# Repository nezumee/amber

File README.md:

# Amber
Personalized split keyboard based on [Zebra](https://github.com/nezumee/zebra) experimentation.

# Bill of material

* PCB x2, switch plate PCB x2, bottom plate PCB x2 (see [gerber](gerber), all PCBs are reversible)
* ProMicro or equivalent x2 (if using something other than ProMicro, check if it will fit in the PCB cutout!)
* Peel-A-Way sockets x48 pins (https://keeb.io/products/peel-a-way-sockets-for-pro-micros)
* Mid-mount TRRS jack x2 (https://www.digikey.com/en/products/detail/cui-devices/SJ-43504-SMT-TR/2625173 or PJ342C in https://www.aliexpress.com/item/1005001299482943.html)
* Tactile switch x2 (https://www.digikey.com/en/products/detail/panasonic-electronic-components/EVQ-P7C01P/4429458)
* RGB LED x2 (https://www.digikey.com/en/products/detail/inolux/HV-5RGB60/7604616 or compatible)
* 1k Ohm resistor in 1206 size x2 (or other value, depending on how bright you want the indicator LED to be)
* EC11 rotary encoders x0-2
* N4148 x32 in DO-35 (through hole) or SOD123 (surface mount) form factor
* KailH sockets x32-34 (you need less than 34 if using encoders)
* Cherry MX compatible switches x32-34
* Keycaps
* TRRS cable

# Making a PCB sandwich keyboard starting with an ergogen definition
This design was created with help of the https://github.com/mrzealot/ergogen tool that makes it easier to generate keyboard plates and PCBs.

Rough steps used:
1. Generate PCB and outlines using ergogen: [ergogen.yaml](ergogen.yaml)
2. Create a Kicad schematic with switches and diodes, matching the ids created by ergogen, make a PCB based on that
3. Overwrite the Kicad PCB with the one coming from ergogen
4. Update PCB from schematic, preserving references but updating the nets and footprints as needed
5. Import the edges layer from ergogen outline, keep default position so outline matches the switch positions
6. Continue designing the PCB in Kicad as normal

# Fitting the ProMicro between the switch plate and PCB
Many keyboards using ProMicro (like Corne) either have the ProMicro exposed, or use a small plate to cover it separately from the switch plate. While the tech prototype look of showing the MCU is nice, sometimes you want something cleaner looking, and also less prone to gathering visible dust. With this in mind, I decided to make the front plate that serves both as a plate for the switches and also covers all the components on the PCB. This led to a few challenges:

1. Fit the ProMicro and its socket (yes, I didn't want to solder it to the PCB directly) between the PCB and the front plate. This required a surprising amount of effort:
  * Use the thinnest sockets I could find - Peel-a-way sockets (https://keeb.io/products/peel-a-way-sockets-for-pro-micros). They seem to be difficult to source, luckily I got some beforehand. Note that these sockets require bigger holes than you would normally have. My first iteration of the PCB had too narrow holes so they could not fit. 1.1mm in the second version is enough:

  * Mount ProMicro upside down
  * Make a cutout in the PCB to fit the components on ProMicro
 
  * The cutout and the fact that ProMicro is stuck between switches and the end of the board made routing quite difficult. Leaving a bridge between the left and right pin columns helped, but common ways of making reversible PCBs couldn't work. There is no space for dual ProMicro footprint, and I cannot reverse the ProMicro either since it becomes too tall to fit. I didn't want to mount it below the PCB either since there's even less space there.
  * To make the PCB reversible, I ended up using different pinouts for the left and right halves. For example, the index finger column (CI) is connected to B2 on the left side, but is mirrored to B4 on the right. This solved most of the pins at the cost of complicating firmware. A few that could not be reassigned, like VCC. For those, I added jumpers that are cut and soldered depending on which side is being built. For left side, you connect J1-J3 and cut J4-J6 (default). For the right side, you do the opposite.
 
2. Fit a TRRS jack between the plates. The jack commonly used is even thicker than ProMicro with a socket. Luckily, it turned out there are special mid-mount jacks that mount into a cutout in the PCB: CUI Devices SJ-4350 series available on DigiKey, or PJ342C available on AliExpress (I got both; despite the differences in diagrams on seller sites, the ones I got look identical).

3. Fit a reset button between the plates. This was straightforward, there's a number of thin tactile buttons available. I picked a small switch with button on the side. It turned out to be difficult to press, but I feel it's not a big deal since I don't use it often. Reset command can be added somewhere in the layout if needed.

With this, everything fits between the plates comfortably:

Of course, I waste all this effort by almost always using the keyboard with tented legs, attached using magnets: [Things/Tented-base.stl](Things/Tented-base.stl).

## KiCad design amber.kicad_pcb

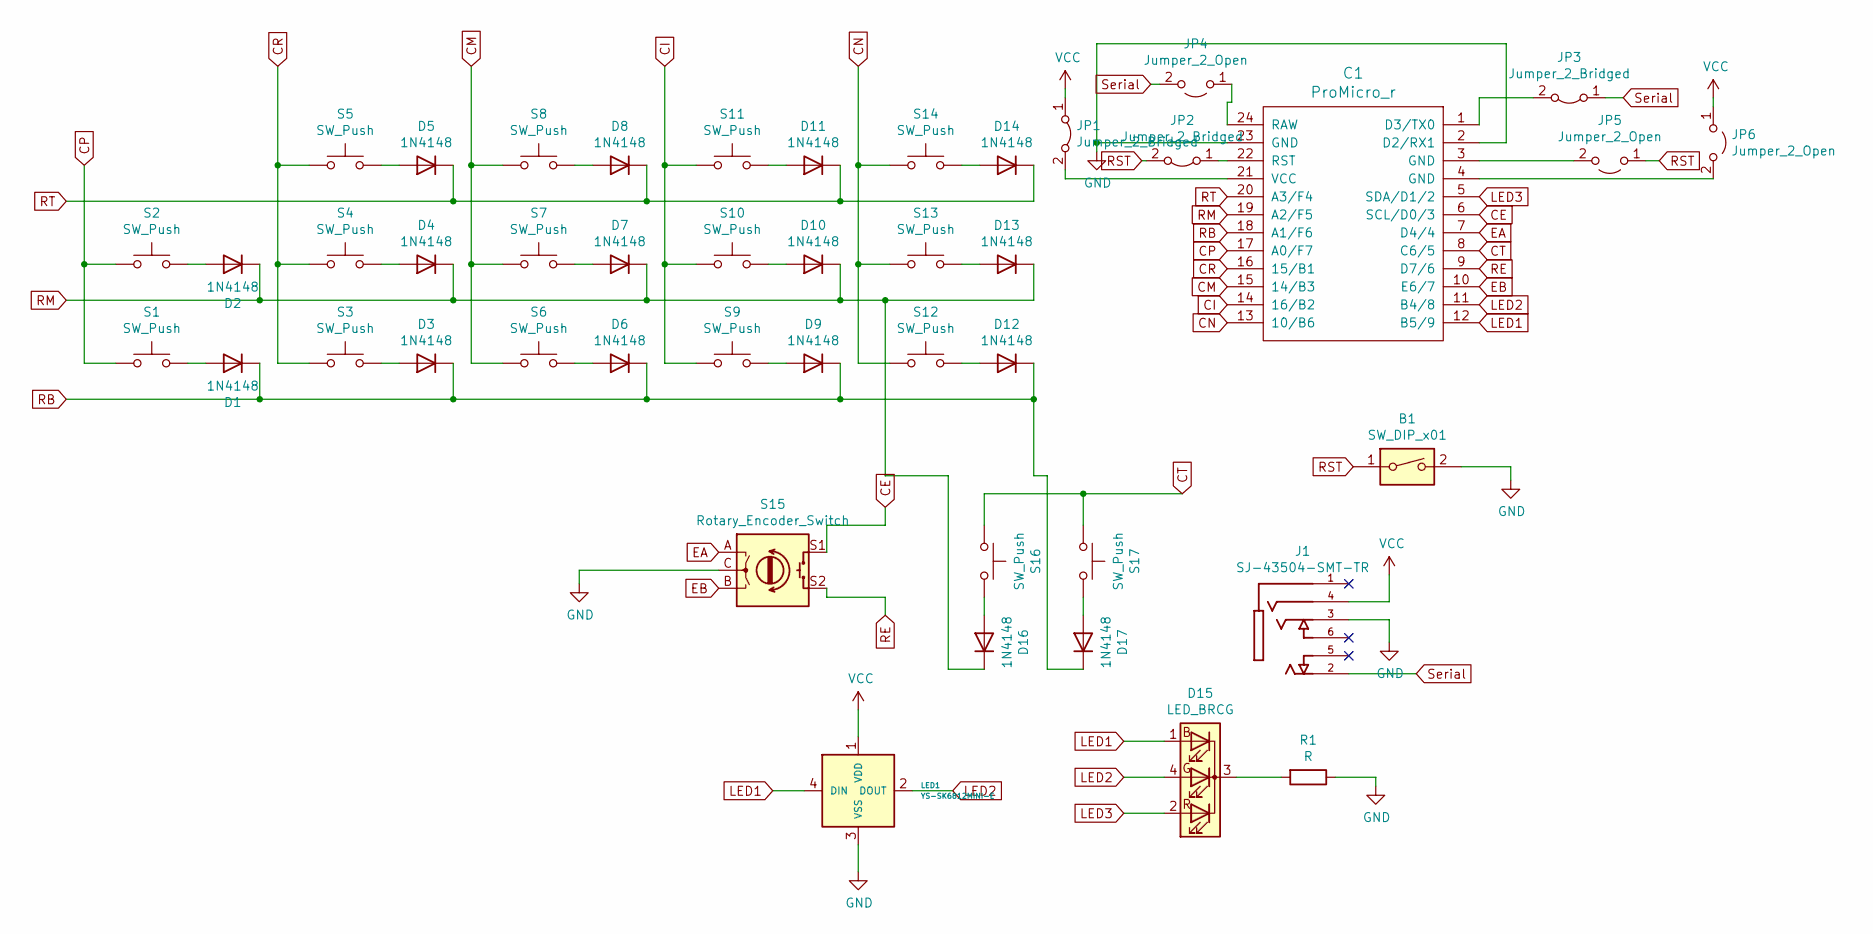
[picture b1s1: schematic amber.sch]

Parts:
B1: SW_DIP_x01; SW_SPST_EVQP7C
C1: ProMicro_r; ProMicro
D1, D2, D3, D4, D5, D6, D7, D8, D9, D10, D11, D12, D13, D14, D16, D17: 1N4148; Diode_THT7.6_SOD123
D15: LED_BRCG; LED_D5.0mm-4_RGB_Wide_Pins-dual
J1: SJ-43504-SMT-TR; CUI_SJ-43504-SMT-TR-dual
JP1, JP2, JP3: Jumper_2_Bridged; SolderJumper-2_P1.3mm_Bridged_Pad1.0x1.5mm
JP4, JP5, JP6: Jumper_2_Open; SolderJumper-2_P1.3mm_Open_Pad1.0x1.5mm
LED1: YS-SK6812MINI-E; LED_WS2812B-PLCC4-dual
R1: R; R_1206_3216Metric_Pad1.30x1.75mm_HandSolder
S1, S2, S3, S4, S5, S6, S7, S8, S9, S10, S11, S12, S13, S14, S16, S17: SW_Push; CherryMX_MidHeight_Hotswap
S15: Rotary_Encoder_Switch; Switch_MX2side_Encoder

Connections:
CE: C1.6 (SCL/D0/3), S15.S1
CI: C1.14 (16/B2), S9.1, S10.1, S11.1
CM: C1.15 (14/B3), S6.1, S7.1, S8.1
CN: C1.13 (10/B6), S12.1, S13.1, S14.1
CP: C1.17 (A0/F7), S1.1, S2.1
CR: C1.16 (15/B1), S3.1, S4.1, S5.1
CT: C1.8 (C6/5), S16.1, S17.1
EA: C1.7 (D4/4), S15.A
EB: C1.10 (E6/7), S15.B
GND: B1.2, C1.2 (D2/RX1), C1.23 (GND), J1.3, LED1.3 (VSS), R1.1, S15.C
LED1: C1.12 (B5/9), D15.1 (BA), LED1.4 (DIN)
LED2: C1.11 (B4/8), D15.4 (GA), LED1.2 (DOUT)
LED3: C1.5 (SDA/D1/2), D15.2 (RA)
unnamed: C1.1 (D3/TX0), JP3.2 (B)
unnamed: C1.3 (GND), JP5.2 (B)
unnamed: C1.4 (GND), JP6.2 (B)
unnamed: C1.21 (VCC), JP1.2 (B)
unnamed: C1.22 (RST), JP2.1 (A)
unnamed: C1.24 (RAW), JP4.1 (A)
unnamed: D1.2 (A), S1.2
unnamed: D2.2 (A), S2.2
unnamed: D3.2 (A), S3.2
unnamed: D4.2 (A), S4.2
unnamed: D5.2 (A), S5.2
unnamed: D6.2 (A), S6.2
unnamed: D7.2 (A), S7.2
unnamed: D8.2 (A), S8.2
unnamed: D9.2 (A), S9.2
unnamed: D10.2 (A), S10.2
unnamed: D11.2 (A), S11.2
unnamed: D12.2 (A), S12.2
unnamed: D13.2 (A), S13.2
unnamed: D14.2 (A), S14.2
unnamed: D15.3 (K), R1.2
unnamed: D16.2 (A), S16.2
unnamed: D17.2 (A), S17.2
RB: C1.18 (A1/F6), D1.1 (K), D3.1 (K), D6.1 (K), D9.1 (K), D12.1 (K), D17.1 (K)
RE: C1.9 (D7/6), S15.S2
RM: C1.19 (A2/F5), D2.1 (K), D4.1 (K), D7.1 (K), D10.1 (K), D13.1 (K), D16.1 (K)
RST: B1.1, JP2.2 (B), JP5.1 (A)
RT: C1.20 (A3/F4), D5.1 (K), D8.1 (K), D11.1 (K), D14.1 (K)
Serial: J1.2, JP3.1 (A), JP4.2 (B)
VCC: J1.4, JP1.1 (A), JP6.1 (A), LED1.1 (VDD)

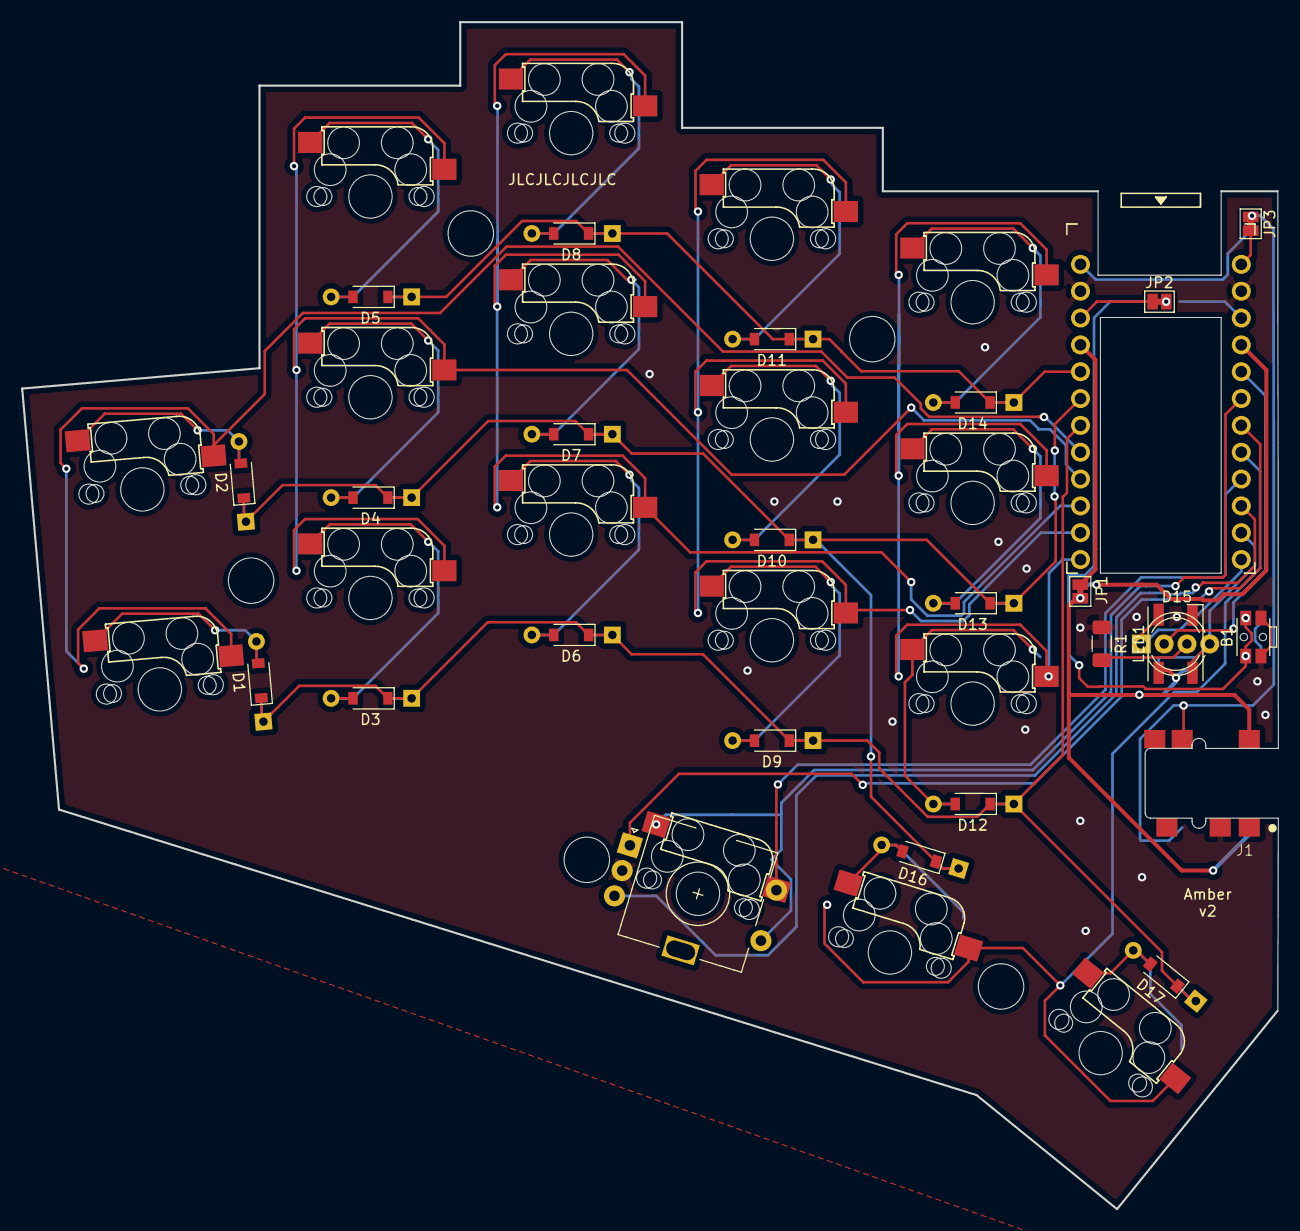
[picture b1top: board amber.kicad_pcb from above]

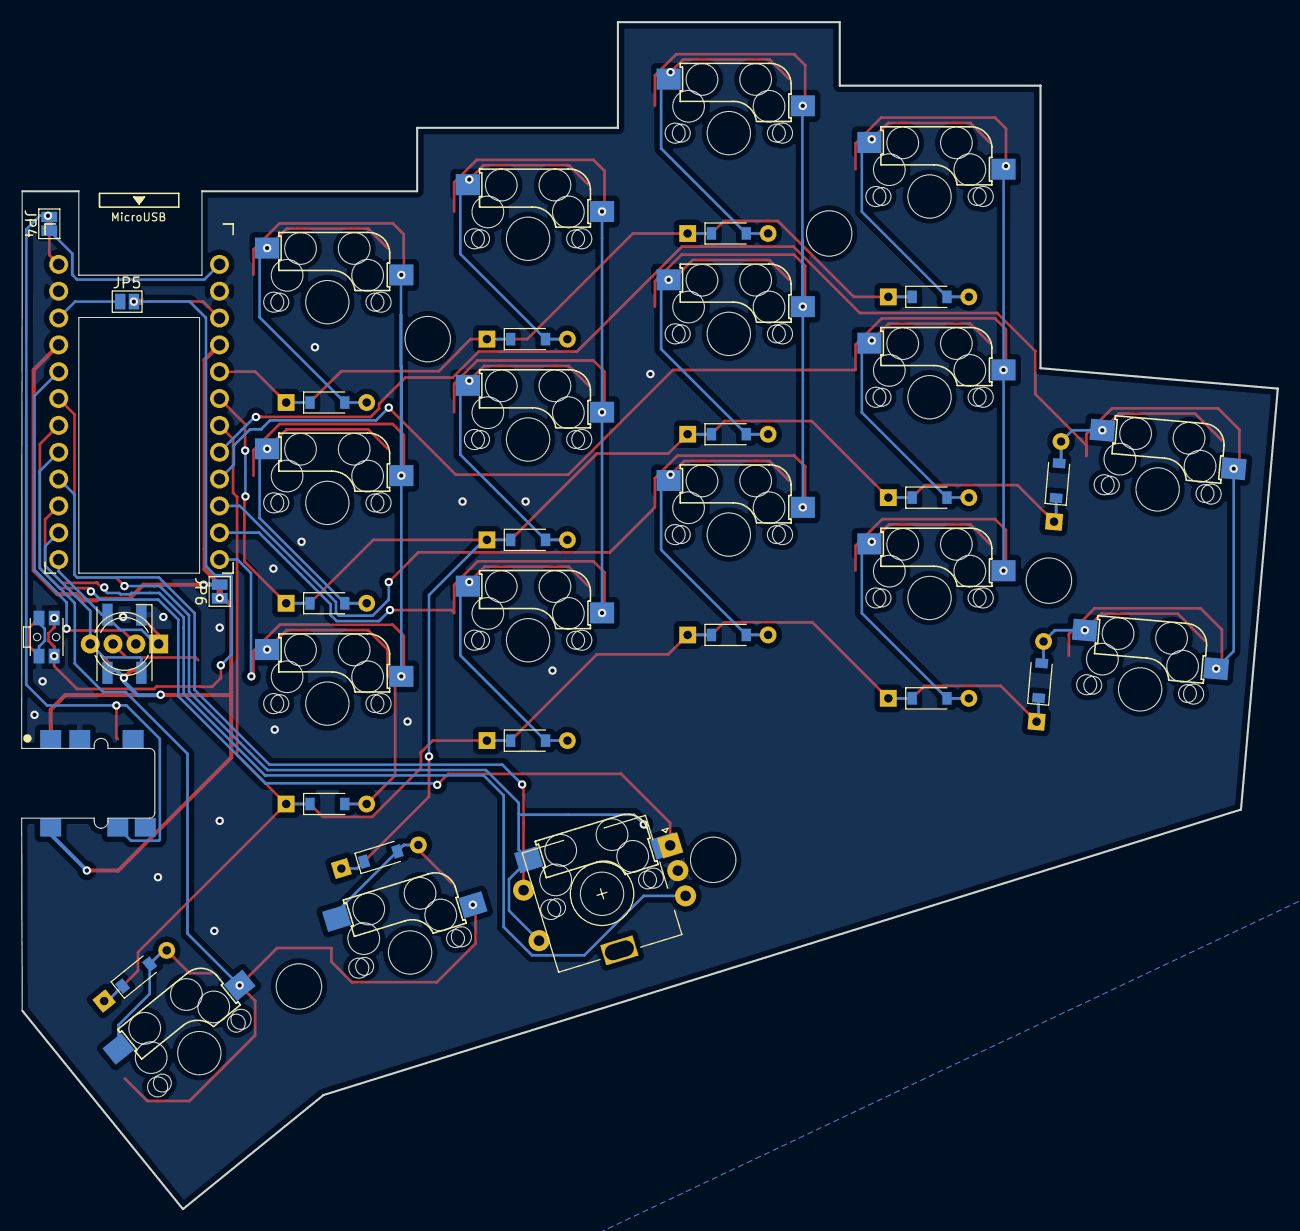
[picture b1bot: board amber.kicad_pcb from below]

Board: 2 copper layers, 118.8 x 112.3 mm, 50 parts (3 on the bottom side), 43 nets.

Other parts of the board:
P1, P2, P3, P4, P5: M2_HOLE_v2

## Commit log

2021-02-08 Add Amber v1
2021-03-08 Add case drawings
2021-03-08 Use a mid-mount TRRS jack SJ 43504
2021-03-08 Widen the promicro pad holes
2021-03-08 Move serial to D1
2021-03-08 Add magnets, use side switch for reset
2021-03-08 Prettify the ground vias
2021-03-09 Update silkscreen
2021-03-09 Make a reversible MCU socket using jumpers
2021-03-14 Fix the encoder/switch footprint
2021-03-14 Let standoffs go through the PCB
2021-03-14 Remove the reset button cutout in the plate
2021-03-14 Add bottom plate
2021-03-14 Update metadata
2021-03-15 Replace 2 LEDs with one 5mm
2021-03-15 Add a pixel LED indicator option
2021-03-15 Make pixel LEDs easier to solder
2021-03-15 Cleanup tracks
2021-03-15 Add a plate with rough extension for gasket mount
2021-03-15 Create gerbers for v2
    Also shorten a gasket mount flap a bit in extended plate
2021-03-28 Move magnets to where they can be added in the tented print
2021-03-28 Add images
2021-03-28 Fix image links
2021-03-29 Add the firmware
2021-03-29 Add tented base
2021-08-01 Update .gitignore
    Ignore temporary outputs
2021-08-01 Add metal case files
